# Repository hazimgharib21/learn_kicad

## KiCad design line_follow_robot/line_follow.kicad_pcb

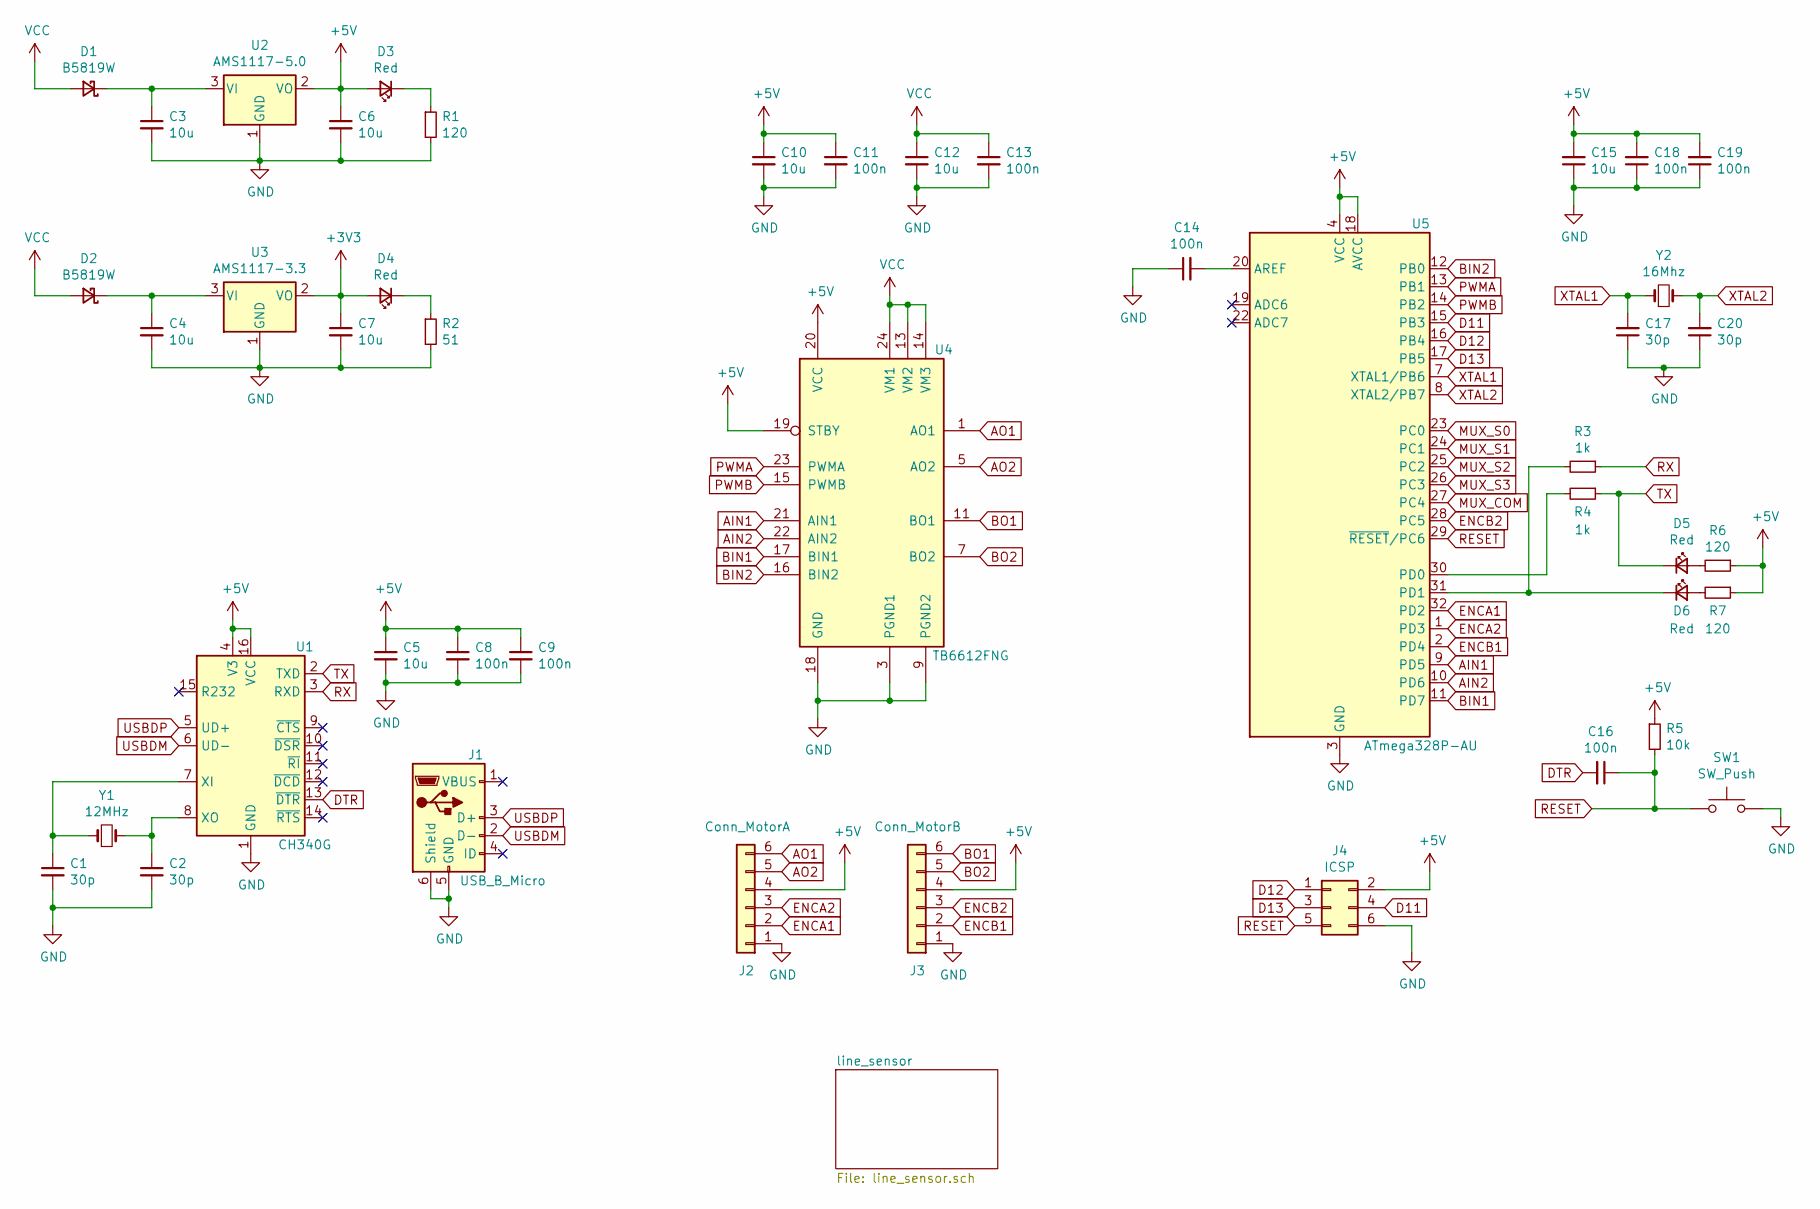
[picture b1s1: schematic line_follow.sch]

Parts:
C1, C2, C17, C20: 30p; C_0805_2012Metric
C3, C4, C5, C6, C7, C10, C12, C15: 10u; C_0805_2012Metric
C8, C9, C11, C13, C14, C16, C18, C19: 100n; C_0603_1608Metric
D1, D2: B5819W; D_SOD-123
D3, D4, D5, D6: Red; LED_1206_3216Metric
J1: USB_B_Micro; USB_Micro-B_Amphenol_10103594-0001LF_Horizontal
J2: Conn_MotorA; PinHeader_1x06_P1.00mm_Vertical
J3: Conn_MotorB; PinHeader_1x06_P1.00mm_Vertical
J4: ICSP; PinHeader_2x03_P2.00mm_Vertical
R1, R6, R7: 120; R_0603_1608Metric
R2: 51; R_0805_2012Metric
R3, R4: 1k; R_0603_1608Metric
R5: 10k; R_1206_3216Metric
SW1: SW_Push; SW_SPST_FSMSM
U1: CH340G; SOIC-16_3.9x9.9mm_P1.27mm
U2: AMS1117-5.0; SOT-223-3_TabPin2
U3: AMS1117-3.3; SOT-223-3_TabPin2
U4: TB6612FNG; SSOP-24_5.3x8.2mm_P0.65mm
U5: ATmega328P-AU; TQFP-32_7x7mm_P0.8mm
Y1: 12MHz; Crystal_SMD_HC49-SD
Y2: 16Mhz; Crystal_SMD_5032-2Pin_5.0x3.2mm

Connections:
+3V3: C7.1, D4.2 (A), U3.2 (VO)
+5V: C5.1, C6.1, C8.1, C9.1, C10.1, C11.1, C15.2, C18.2, C19.2, D3.2 (A), J2.4, J3.4, J4.2, R5.1, R6.1, R7.1, U1.4 (V3), U1.16 (VCC), U2.2 (VO), U4.19 (STBY), U4.20 (VCC), U5.4 (VCC), U5.6 (VCC), U5.18 (AVCC); also elsewhere on the board
AIN1: U4.21 (AIN1), U5.9 (PD5)
AIN2: U4.22 (AIN2), U5.10 (PD6)
AO1: J2.6, U4.1 (AO1), U4.2 (AO1)
AO2: J2.5, U4.5 (AO2), U4.6 (AO2)
BIN1: U4.17 (BIN1), U5.11 (PD7)
BIN2: U4.16 (BIN2), U5.12 (PB0)
BO1: J3.6, U4.11 (BO1), U4.12 (BO1)
BO2: J3.5, U4.7 (BO2), U4.8 (BO2)
D11: J4.4, U5.15 (PB3)
D12: J4.1, U5.16 (PB4)
D13: J4.3, U5.17 (PB5)
DTR: C16.2, U1.13 (~DTR)
ENCA1: J2.2, U5.32 (PD2)
ENCA2: J2.3, U5.1 (PD3)
ENCB1: J3.2, U5.2 (PD4)
ENCB2: J3.3, U5.28 (PC5)
GND: C1.2, C2.2, C3.2, C4.2, C5.2, C6.2, C7.2, C8.2, C9.2, C10.2, C11.2, C12.2, C13.2, C14.1, C15.1, C17.1, C18.1, C19.1, C20.1, J1.5 (GND), J1.6 (Shield), J2.1, J3.1, J4.6, R1.2, R2.2, SW1.2, U1.1 (GND), U2.1 (GND), U3.1 (GND), U4.3 (PGND1), U4.4 (PGND1), U4.9 (PGND2), U4.10 (PGND2), U4.18 (GND), U5.3 (GND), U5.5 (GND), U5.21 (GND); also elsewhere on the board
MUX_COM: U5.27 (PC4); also elsewhere on the board
MUX_S0: U5.23 (PC0); also elsewhere on the board
MUX_S1: U5.24 (PC1); also elsewhere on the board
MUX_S2: U5.25 (PC2); also elsewhere on the board
MUX_S3: U5.26 (PC3); also elsewhere on the board
unnamed: C1.1, U1.7 (XI), Y1.1
unnamed: C2.1, U1.8 (XO), Y1.2
unnamed: C3.1, D1.1 (K), U2.3 (VI)
unnamed: C4.1, D2.1 (K), U3.3 (VI)
unnamed: C14.2, U5.20 (AREF)
unnamed: D3.1 (K), R1.1
unnamed: D4.1 (K), R2.1
unnamed: D5.2 (A), R6.2
unnamed: D6.1 (K), R3.2, U5.31 (PD1)
unnamed: D6.2 (A), R7.2
unnamed: R4.2, U5.30 (PD0)
PWMA: U4.23 (PWMA), U5.13 (PB1)
PWMB: U4.15 (PWMB), U5.14 (PB2)
RESET: C16.1, J4.5, R5.2, SW1.1, U5.29 (~RESET~/PC6)
RX: R3.1, U1.3 (RXD)
TX: D5.1 (K), R4.1, U1.2 (TXD)
USBDM: J1.2 (D-), U1.6 (UD-)
USBDP: J1.3 (D+), U1.5 (UD+)
VCC: C12.1, C13.1, D1.2 (A), D2.2 (A), U4.13 (VM2), U4.14 (VM3), U4.24 (VM1)
XTAL1: C17.2, U5.7 (XTAL1/PB6), Y2.1
XTAL2: C20.2, U5.8 (XTAL2/PB7), Y2.2

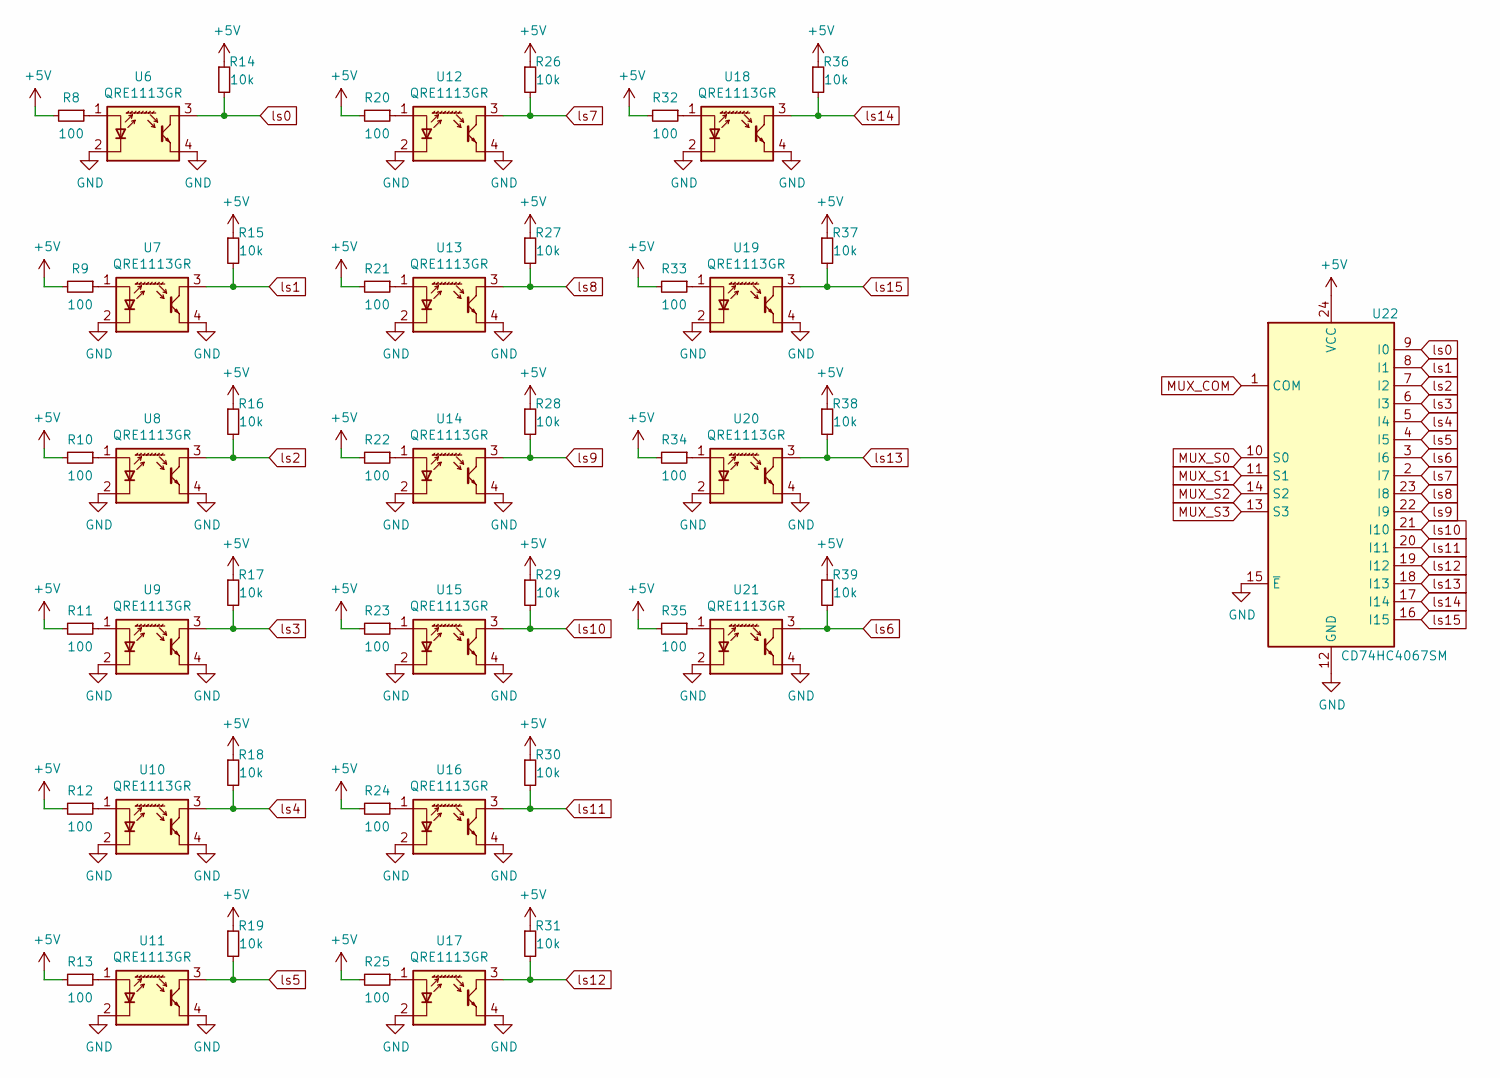
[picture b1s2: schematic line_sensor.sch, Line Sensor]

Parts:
R8, R9, R10, R11, R12, R13, R20, R21, R22, R23, R24, R25, R32, R33, R34, R35: 100; R_1206_3216Metric
R14, R15, R16, R17, R18, R19, R26, R27, R28, R29, R30, R31, R36, R37, R38, R39: 10k; R_1206_3216Metric
U6, U7, U8, U9, U10, U11, U12, U13, U14, U15, U16, U17, U18, U19, U20, U21: QRE1113GR; OnSemi_CASE100CY
U22: CD74HC4067SM; SSOP-24_5.3x8.2mm_P0.65mm

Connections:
+5V: R8.2, R9.2, R10.2, R11.2, R12.2, R13.2, R14.1, R15.1, R16.1, R17.1, R18.1, R19.1, R20.2, R21.2, R22.2, R23.2, R24.2, R25.2, R26.1, R27.1, R28.1, R29.1, R30.1, R31.1, R32.2, R33.2, R34.2, R35.2, R36.1, R37.1, R38.1, R39.1, U22.24 (VCC); also elsewhere on the board
GND: U6.2 (K), U6.4, U7.2 (K), U7.4, U8.2 (K), U8.4, U9.2 (K), U9.4, U10.2 (K), U10.4, U11.2 (K), U11.4, U12.2 (K), U12.4, U13.2 (K), U13.4, U14.2 (K), U14.4, U15.2 (K), U15.4, U16.2 (K), U16.4, U17.2 (K), U17.4, U18.2 (K), U18.4, U19.2 (K), U19.4, U20.2 (K), U20.4, U21.2 (K), U21.4, U22.12 (GND), U22.15 (~E); also elsewhere on the board
MUX_COM: U22.1 (COM); also elsewhere on the board
MUX_S0: U22.10 (S0); also elsewhere on the board
MUX_S1: U22.11 (S1); also elsewhere on the board
MUX_S2: U22.14 (S2); also elsewhere on the board
MUX_S3: U22.13 (S3); also elsewhere on the board
unnamed: R8.1, U6.1 (A)
unnamed: R9.1, U7.1 (A)
unnamed: R10.1, U8.1 (A)
unnamed: R11.1, U9.1 (A)
unnamed: R12.1, U10.1 (A)
unnamed: R13.1, U11.1 (A)
unnamed: R20.1, U12.1 (A)
unnamed: R21.1, U13.1 (A)
unnamed: R22.1, U14.1 (A)
unnamed: R23.1, U15.1 (A)
unnamed: R24.1, U16.1 (A)
unnamed: R25.1, U17.1 (A)
unnamed: R32.1, U18.1 (A)
unnamed: R33.1, U19.1 (A)
unnamed: R34.1, U20.1 (A)
unnamed: R35.1, U21.1 (A)
ls0: R14.2, U6.3, U22.9 (I0)
ls1: R15.2, U7.3, U22.8 (I1)
ls2: R16.2, U8.3, U22.7 (I2)
ls3: R17.2, U9.3, U22.6 (I3)
ls4: R18.2, U10.3, U22.5 (I4)
ls5: R19.2, U11.3, U22.4 (I5)
ls6: R39.2, U21.3, U22.3 (I6)
ls7: R26.2, U12.3, U22.2 (I7)
ls8: R27.2, U13.3, U22.23 (I8)
ls9: R28.2, U14.3, U22.22 (I9)
ls10: R29.2, U15.3, U22.21 (I10)
ls11: R30.2, U16.3, U22.20 (I11)
ls12: R31.2, U17.3, U22.19 (I12)
ls13: R38.2, U20.3, U22.18 (I13)
ls14: R36.2, U18.3, U22.17 (I14)
ls15: R37.2, U19.3, U22.16 (I15)

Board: 2 copper layers, 94 parts (0 on the bottom side), 77 nets, no tracks yet.

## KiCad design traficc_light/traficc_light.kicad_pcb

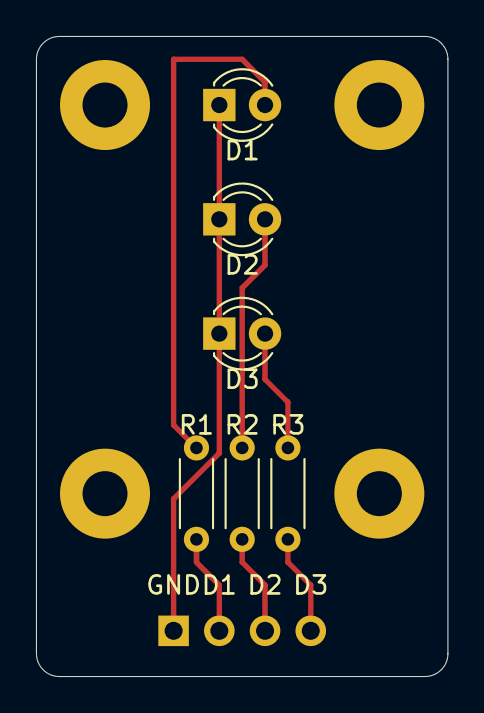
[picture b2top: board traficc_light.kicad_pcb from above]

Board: 2 copper layers, 22.9 x 35.6 mm, 11 parts (1 on the bottom side), 7 nets.

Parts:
D1, D2, D3: LED; LED_D3.0mm
H1, H2, H3, H4: MountingHole; MountingHole_2.5mm_Pad
J1: Conn_01x04; PinHeader_1x04_P2.54mm_Horizontal
R1, R2, R3: R; R_Axial_DIN0204_L3.6mm_D1.6mm_P5.08mm_Horizontal

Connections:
unnamed: D1.1, D2.1, D3.1, J1.1
unnamed: D1.2, R1.1
unnamed: D2.2, R2.1
unnamed: D3.2, R3.1
unnamed: J1.2, R1.2
unnamed: J1.3, R2.2
unnamed: J1.4, R3.2

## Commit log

2020-12-29 added stm32f405 breakout schematic
2020-12-30 added trafic light pcb
2021-01-01 add line follow robot
